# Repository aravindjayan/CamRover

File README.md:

# camRover

camRover is an ESP32-S3 rover platform with an OV7670 camera, two encoder-equipped DC motors, and addressable RGB LEDs. This repository contains the KiCad hardware design, release manufacturing files, and Arduino firmware used to bring up and test the board.

## Repository contents

- [`board_bringup/`](board_bringup/) — Arduino ESP32-S3 firmware for camera streaming over Wi-Fi and testing motors, quadrature encoders, and LEDs.
- [`camRover_pcb/camRover_pcb_v1_1/`](camRover_pcb/camRover_pcb_v1_1/) — KiCad v1.1 project, hierarchical schematics, PCB layout, assembly files, stencil outputs, and release Gerbers/drill files.
- [`camrover_img.jpg`](camrover_img.jpg) — photo of the built rover.

## Board bring-up firmware

The sketch captures OV7670 RGB565 frames at QVGA (320 × 240), converts them to JPEG, and serves a browser-based test page. The page shows the live video and provides motor pulses, encoder tests, and RGB LED controls. Motor commands have a 2-second firmware watchdog.

### Build with Arduino IDE

Build tested with **Arduino-ESP32 3.3.12**.

1. Open `board_bringup/board_bringup.ino` in Arduino IDE. Keep `sccb_ov7670_compat.cpp` in the same sketch folder.
2. Install/select the **Arduino-ESP32 3.3.12** board package.
3. Select **ESP32S3 Dev Module** and set:

   | Setting | Value |
   |---|---|
   | Flash Size | `16MB (128Mb)` |
   | PSRAM | `OPI PSRAM` |
   | USB CDC On Boot | `Enabled` |

4. Connect the ESP32-S3 board over USB, select its port, then compile and upload.
5. Open Serial Monitor at **115200 baud**. After Wi-Fi connects, open the printed IP address in a browser.

Before uploading, set `WIFI_SSID` and `WIFI_PASSWORD` near the top of `board_bringup.ino` to your 2.4 GHz Wi-Fi credentials. The defaults in the sketch are local development settings; replace them for your network. The rover and browser must be on the same network. If Wi-Fi does not connect, motor and LED serial commands remain available.

Camera orientation and left-edge crop can be adjusted with `CAMERA_ROTATION` (`0`, `90`, `180`, or `270`) and `CAMERA_CROP_LEFT` in the sketch.

### Bring-up controls

The web page provides:

- Live OV7670 video.
- Forward/reverse pulse tests for each motor and both motors together; each web pulse lasts 750 ms.
- Encoder count reset and forward/reverse tests. Lift wheels clear before running encoder tests.
- Red, green, blue, white, and off LED controls.

Serial commands at 115200 baud:

| Command | Action |
|---|---|
| `m <left> <right>` | Drive motors with values from `-255` to `255` (1-second timeout). |
| `s` | Stop motors. |
| `l <r> <g> <b>` | Set all five LEDs; each color value is `0`–`255`. |
| `e` | Print encoder counts. |

### Firmware pin map

| Function | ESP32-S3 GPIO |
|---|---|
| OV7670 D0–D7 | 4, 8, 5, 9, 6, 10, 7, 11 |
| OV7670 XCLK / PCLK / VSYNC / HREF | 13 / 12 / 21 / 14 |
| OV7670 SIOD / SIOC | 16 / 17 |
| Motor 1 DRV8871 IN1 / IN2 | 18 / 15 |
| Motor 2 DRV8871 IN1 / IN2 | 42 / 47 |
| Motor 1 encoder A / B | 41 / 40 |
| Motor 2 encoder A / B | 2 / 1 |
| WS2812B chain DIN (5 LEDs) | 48 |

## PCB files

Open `camRover_pcb/camRover_pcb_v1_1/camRover_pcb_v1_1.kicad_pro` in KiCad. The project includes the main schematic and hierarchical sheets for the ESP32, motor drive, and power circuitry, plus the PCB layout and assembly bill of materials.

The `CamRover_v1_1_Gerbers/` folder and `CamRover_v1_1_Gerbers.zip` contain the release copper, solder mask, paste, silkscreen, board outline, drill files, and drill maps for fabrication. Check the fabrication house’s layer and drill requirements before ordering.

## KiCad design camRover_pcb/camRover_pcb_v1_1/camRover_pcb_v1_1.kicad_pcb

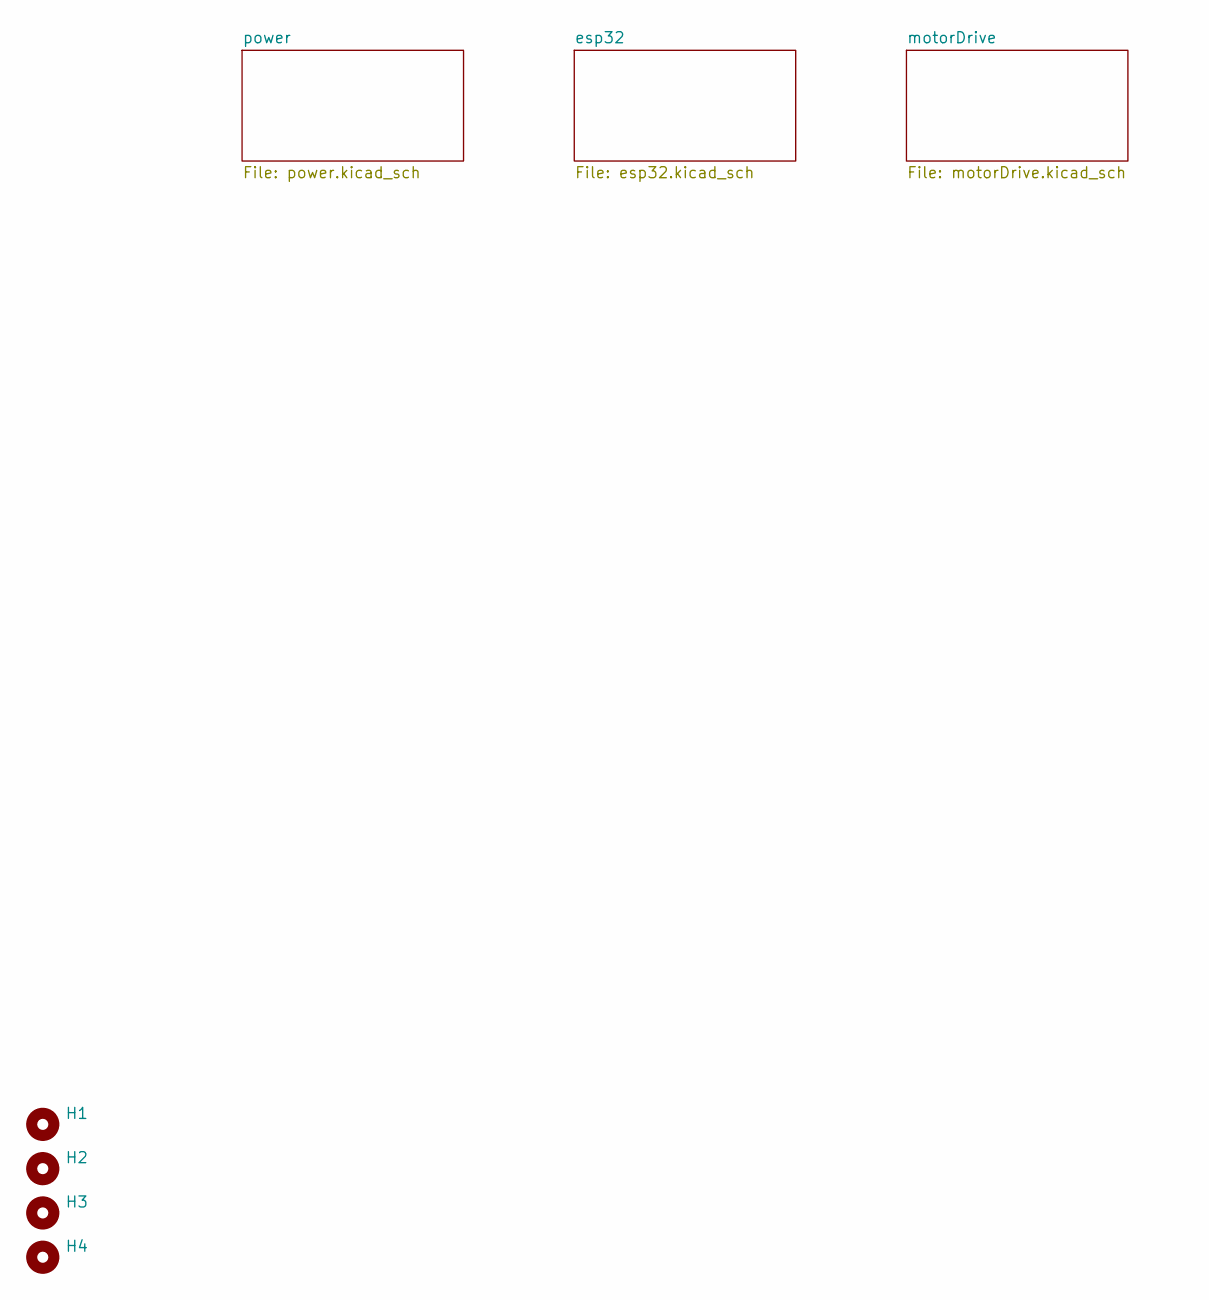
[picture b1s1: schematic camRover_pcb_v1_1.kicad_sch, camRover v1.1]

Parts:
H1, H2, H3, H4: MountingHole; MountingHole_3.2mm_M3

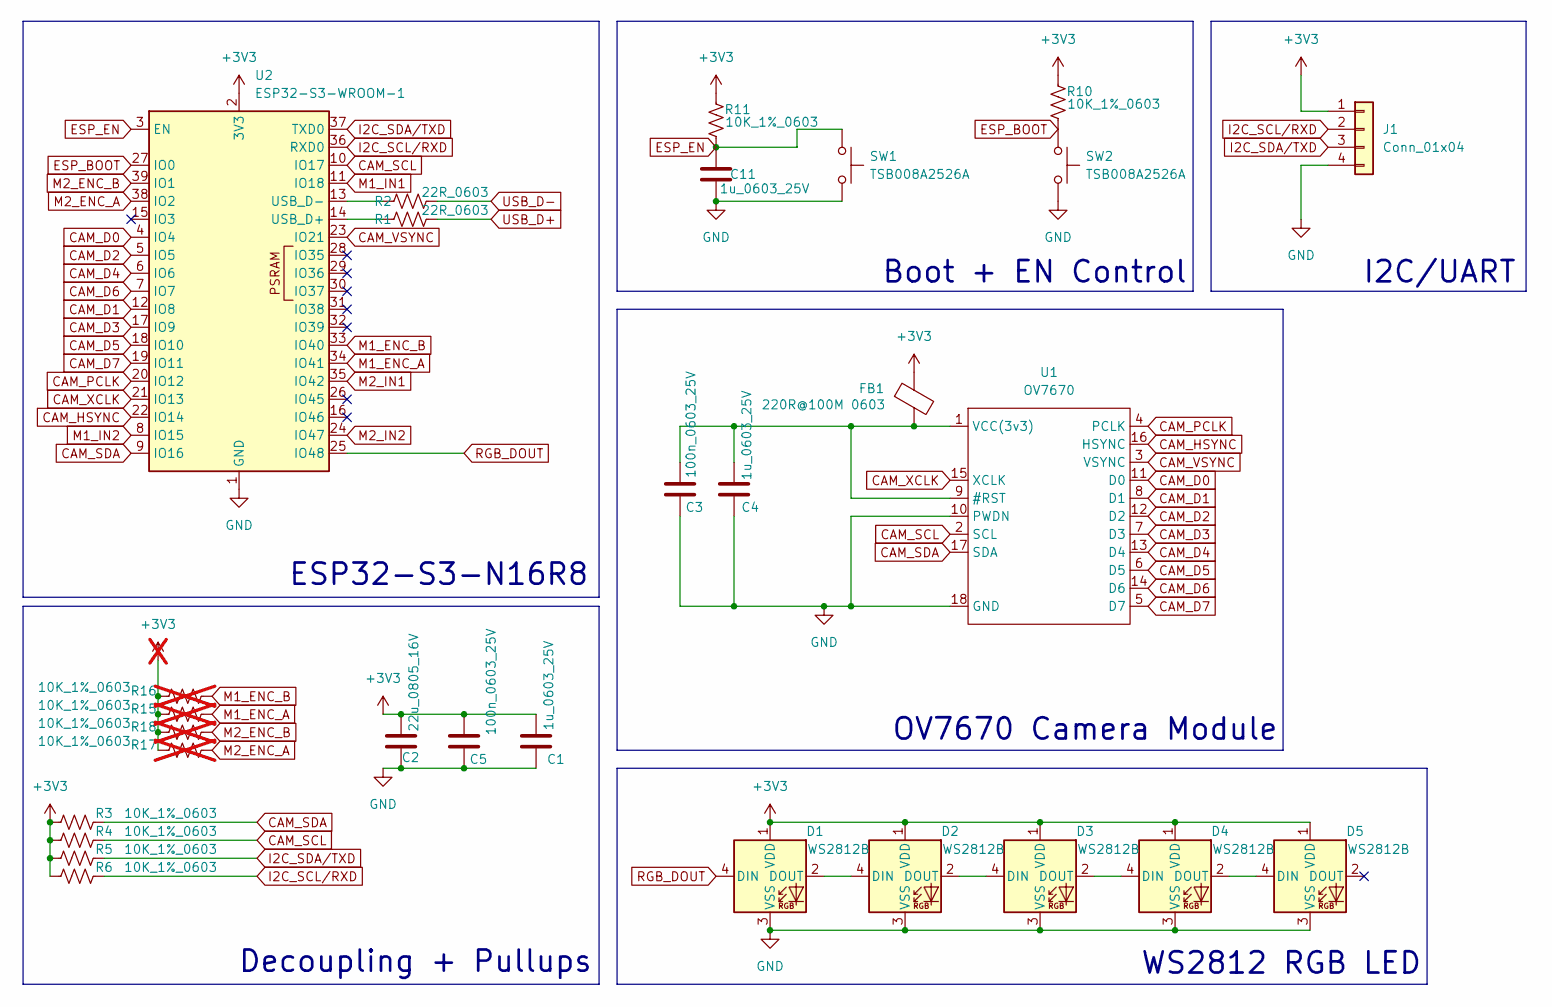
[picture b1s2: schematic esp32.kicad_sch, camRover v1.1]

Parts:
C1, C4, C11: 1u_0603_25V; C_0603_1608Metric
C2: 22u_0805_16V; C_0805_2012Metric
C3, C5: 100n_0603_25V; C_0603_1608Metric
D1, D2, D3, D4, D5: WS2812B; LED_WS2812B_PLCC4_5.0x5.0mm_P3.2mm
FB1: 220R@100M 0603; L_0603_1608Metric
J1: Conn_01x04; PinHeader_1x04_P2.54mm_Vertical
R1, R2: 22R_0603; R_0603_1608Metric
R3, R4, R5, R6, R10, R11: 10K_1%_0603; R_0603_1608Metric
R15, R16, R17, R18: 10K_1%_0603; R_0603_1608Metric; not fitted
SW1, SW2: TSB008A2526A; SW_SPST_CK_RS282G05A3
U1: OV7670; ov7670_dipModule
U2: ESP32-S3-WROOM-1

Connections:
+3V3: C1.1, C2.2, C5.1, D1.1 (VDD), D2.1 (VDD), D3.1 (VDD), D4.1 (VDD), D5.1 (VDD), FB1.1, J1.1, R3.2, R4.2, R5.2, R6.2, R10.1, R11.1, R15.2, R16.2, R17.2, R18.2, U2.2 (3V3); also elsewhere on the board
CAM_D0: U1.11 (D0), U2.4 (IO4)
CAM_D1: U1.8 (D1), U2.12 (IO8)
CAM_D2: U1.12 (D2), U2.5 (IO5)
CAM_D3: U1.7 (D3), U2.17 (IO9)
CAM_D4: U1.13 (D4), U2.6 (IO6)
CAM_D5: U1.6 (D5), U2.18 (IO10)
CAM_D6: U1.14 (D6), U2.7 (IO7)
CAM_D7: U1.5 (D7), U2.19 (IO11)
CAM_HSYNC: U1.16 (HSYNC), U2.22 (IO14)
CAM_PCLK: U1.4 (PCLK), U2.20 (IO12)
CAM_SCL: R4.1, U1.2 (SCL), U2.10 (IO17)
CAM_SDA: R3.1, U1.17 (SDA), U2.9 (IO16)
CAM_VSYNC: U1.3 (VSYNC), U2.23 (IO21)
CAM_XCLK: U1.15 (XCLK), U2.21 (IO13)
ESP_BOOT: R10.2, SW2.1, U2.27 (IO0)
ESP_EN: C11.1, R11.2, SW1.1, U2.3 (EN)
GND: C1.2, C2.1, C3.2, C4.2, C5.2, C11.2, D1.3 (VSS), D2.3 (VSS), D3.3 (VSS), D4.3 (VSS), D5.3 (VSS), J1.4, SW1.2, SW2.2, U1.10 (PWDN), U1.18 (GND), U2.1 (GND), U2.40 (GND), U2.41 (GND); also elsewhere on the board
I2C_SCL/RXD: J1.2, R6.1, U2.36 (RXD0)
I2C_SDA/TXD: J1.3, R5.1, U2.37 (TXD0)
M1_ENC_A: R15.1, U2.34 (IO41); also elsewhere on the board
M1_ENC_B: R16.1, U2.33 (IO40); also elsewhere on the board
M1_IN1: U2.11 (IO18); also elsewhere on the board
M1_IN2: U2.8 (IO15); also elsewhere on the board
M2_ENC_A: R17.1, U2.38 (IO2); also elsewhere on the board
M2_ENC_B: R18.1, U2.39 (IO1); also elsewhere on the board
M2_IN1: U2.35 (IO42); also elsewhere on the board
M2_IN2: U2.24 (IO47); also elsewhere on the board
unnamed: D1.2 (DOUT), D2.4 (DIN)
unnamed: D2.2 (DOUT), D3.4 (DIN)
unnamed: D3.2 (DOUT), D4.4 (DIN)
unnamed: D4.2 (DOUT), D5.4 (DIN)
unnamed: C3.1, C4.1, FB1.2, U1.1 (VCC(3v3)), U1.9 (#RST)
unnamed: R1.1, U2.14 (USB_D+)
unnamed: R2.1, U2.13 (USB_D-)
RGB_DOUT: D1.4 (DIN), U2.25 (IO48)
USB_D+: R1.2; also elsewhere on the board
USB_D-: R2.2; also elsewhere on the board

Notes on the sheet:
I2C/UART
OV7670 Camera Module
Decoupling + Pullups
ESP32-S3-N16R8
WS2812 RGB LED
Boot + EN Control

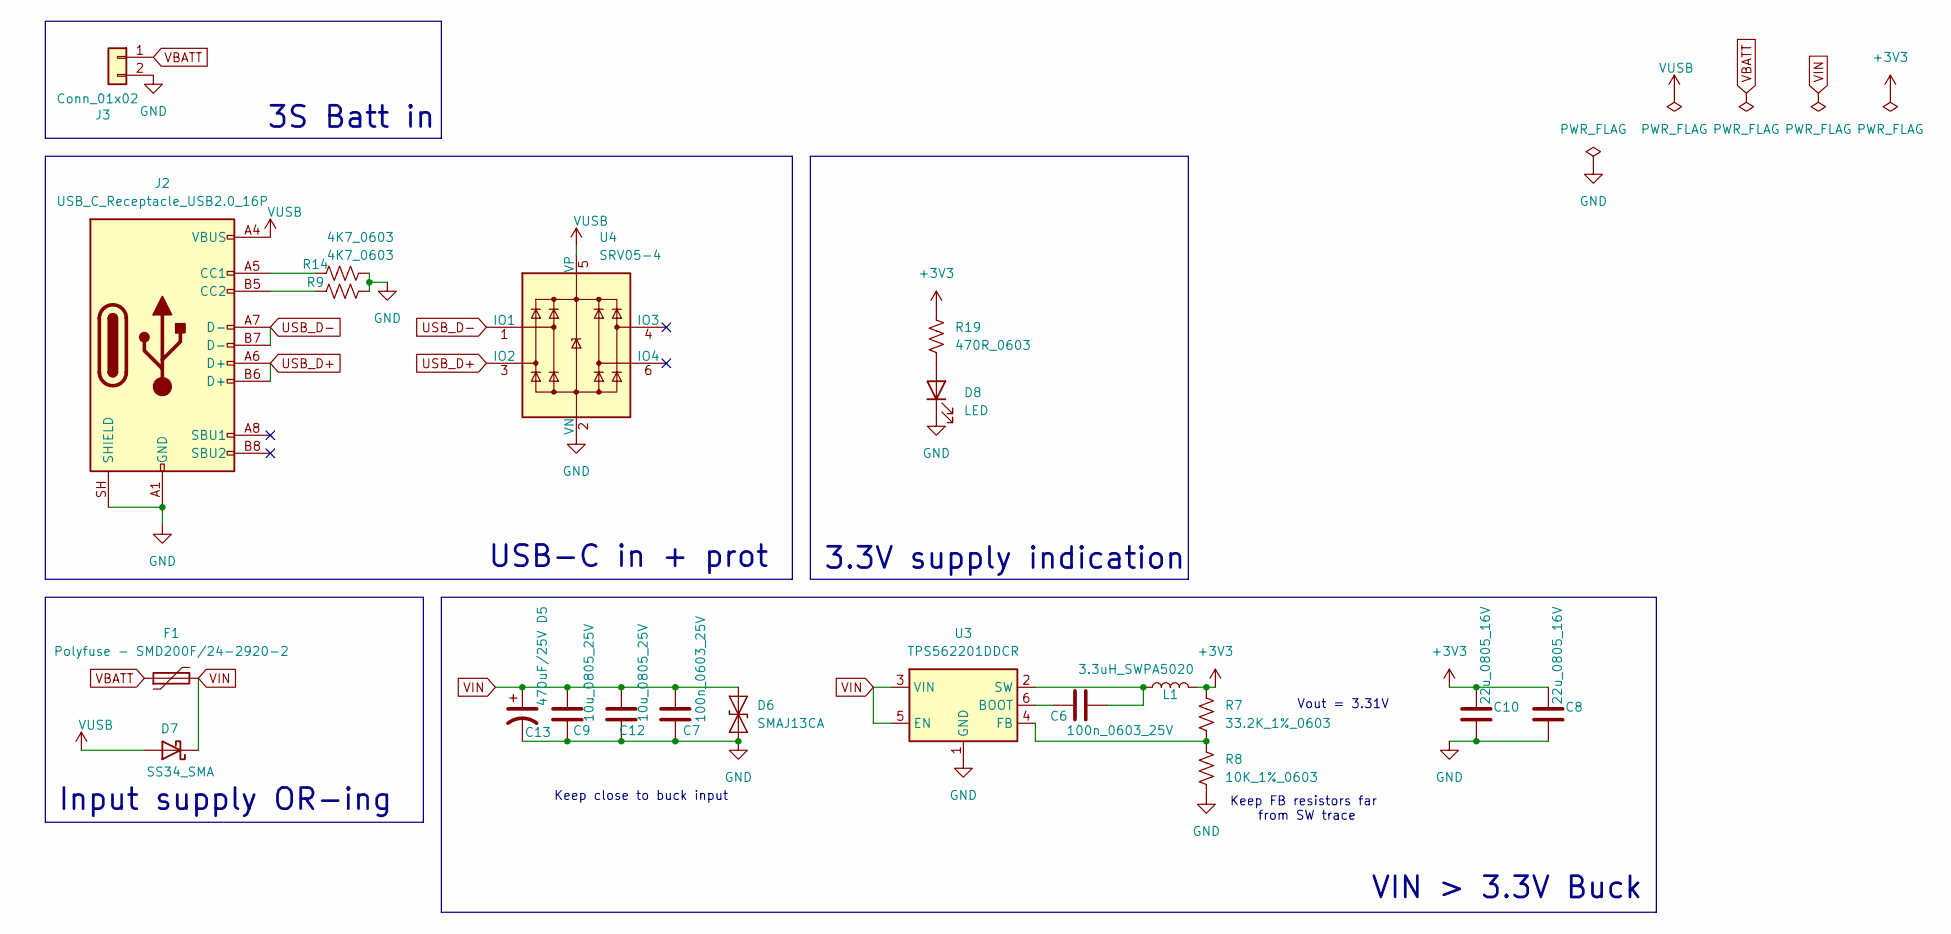
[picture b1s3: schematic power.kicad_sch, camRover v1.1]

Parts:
C6, C7: 100n_0603_25V; C_0603_1608Metric
C8, C10: 22u_0805_16V; C_0805_2012Metric
C9, C12: 10u_0805_25V; C_0805_2012Metric
C13: 470uF/25V D5; CP_Radial_D6.3mm_P2.50mm
D6: SMAJ13CA; D_SMA
D7: SS34_SMA; D_SMA
D8: LED; LED_0805_2012Metric
F1: Polyfuse - SMD200F/24-2920-2; Fuse_2920_7451Metric
J2: USB_C_Receptacle_USB2.0_16P; USB_C_Receptacle_U263-163N-4WS1735-XKB
J3: Conn_01x02; SolderWire-1.5sqmm_1x02_P7.8mm_D1.7mm_OD3.9mm
L1: 3.3uH_SWPA5020; L_Sunlord_SWPA5020S
R7: 33.2K_1%_0603; R_0603_1608Metric
R8: 10K_1%_0603; R_0603_1608Metric
R9, R14: 4K7_0603; R_0603_1608Metric
R19: 470R_0603; R_0603_1608Metric
U3: TPS562201DDCR; SOT-23-6
U4: SRV05-4; SOT-23-6

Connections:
+3V3: C8.2, C10.2, L1.2, R7.2, R19.2; also elsewhere on the board
GND: C7.2, C8.1, C9.2, C10.1, C12.2, C13.2, D6.1 (A1), D8.1 (K), J2.A1 (GND), J2.A12 (GND), J2.B1 (GND), J2.B12 (GND), J2.SH (SHIELD), J3.2, R8.1, R9.2, R14.2, U3.1 (GND), U4.2 (VN); also elsewhere on the board
unnamed: D8.2 (A), R19.1
unnamed: J2.A5 (CC1), R14.1
unnamed: J2.B5 (CC2), R9.1
unnamed: C6.1, U3.6 (BOOT)
unnamed: R7.1, R8.2, U3.4 (FB)
unnamed: C6.2, L1.1, U3.2 (SW)
USB_D+: J2.A6 (D+), J2.B6 (D+), U4.3 (IO2); also elsewhere on the board
USB_D-: J2.A7 (D-), J2.B7 (D-), U4.1 (IO1); also elsewhere on the board
VBATT: F1.1, J3.1
VIN: C7.1, C9.1, C12.1, C13.1, D6.2 (A2), D7.1 (K), F1.2, U3.3 (VIN), U3.5 (EN); also elsewhere on the board
VUSB: D7.2 (A), J2.A4 (VBUS), J2.A9 (VBUS), J2.B4 (VBUS), J2.B9 (VBUS), U4.5 (VP)

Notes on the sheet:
3S Batt in
Keep close to buck input
VIN > 3.3V Buck
Vout = 3.31V
USB-C in + prot
Keep FB resistors far from SW trace
Input supply OR-ing
3.3V supply indication

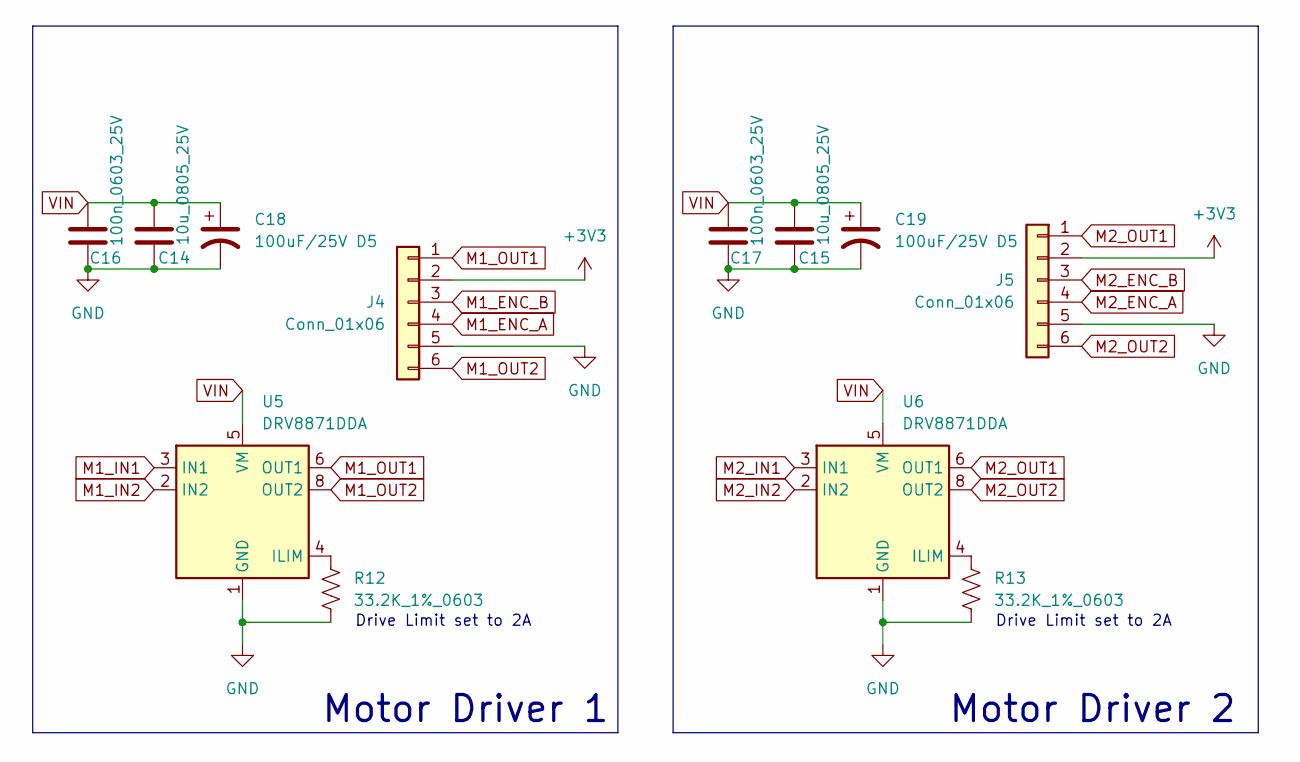
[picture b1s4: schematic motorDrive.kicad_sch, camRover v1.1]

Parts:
C14, C15: 10u_0805_25V; C_0805_2012Metric
C16, C17: 100n_0603_25V; C_0603_1608Metric
C18, C19: 100uF/25V D5; CP_Radial_D5.0mm_P2.00mm
J4, J5: Conn_01x06; 6pin_wireConn_2.54p
R12, R13: 33.2K_1%_0603; R_0603_1608Metric
U5, U6: DRV8871DDA; Texas_HTSOP-8-1EP_3.9x4.9mm_P1.27mm_EP2.95x4.9mm_Mask2.4x3.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

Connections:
+3V3: J4.2, J5.2; also elsewhere on the board
GND: C14.2, C15.2, C16.2, C17.2, C18.2, C19.2, J4.5, J5.5, R12.1, R13.1, U5.1 (GND), U5.7 (GND), U5.9 (GND), U6.1 (GND), U6.7 (GND), U6.9 (GND); also elsewhere on the board
M1_ENC_A: J4.4; also elsewhere on the board
M1_ENC_B: J4.3; also elsewhere on the board
M1_IN1: U5.3 (IN1); also elsewhere on the board
M1_IN2: U5.2 (IN2); also elsewhere on the board
M1_OUT1: J4.1, U5.6 (OUT1)
M1_OUT2: J4.6, U5.8 (OUT2)
M2_ENC_A: J5.4; also elsewhere on the board
M2_ENC_B: J5.3; also elsewhere on the board
M2_IN1: U6.3 (IN1); also elsewhere on the board
M2_IN2: U6.2 (IN2); also elsewhere on the board
M2_OUT1: J5.1, U6.6 (OUT1)
M2_OUT2: J5.6, U6.8 (OUT2)
unnamed: R12.2, U5.4 (ILIM)
unnamed: R13.2, U6.4 (ILIM)
VIN: C14.1, C15.1, C16.1, C17.1, C18.1, C19.1, U5.5 (VM), U6.5 (VM); also elsewhere on the board

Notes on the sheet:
Drive Limit set to 2A
Motor Driver 2
Motor Driver 1

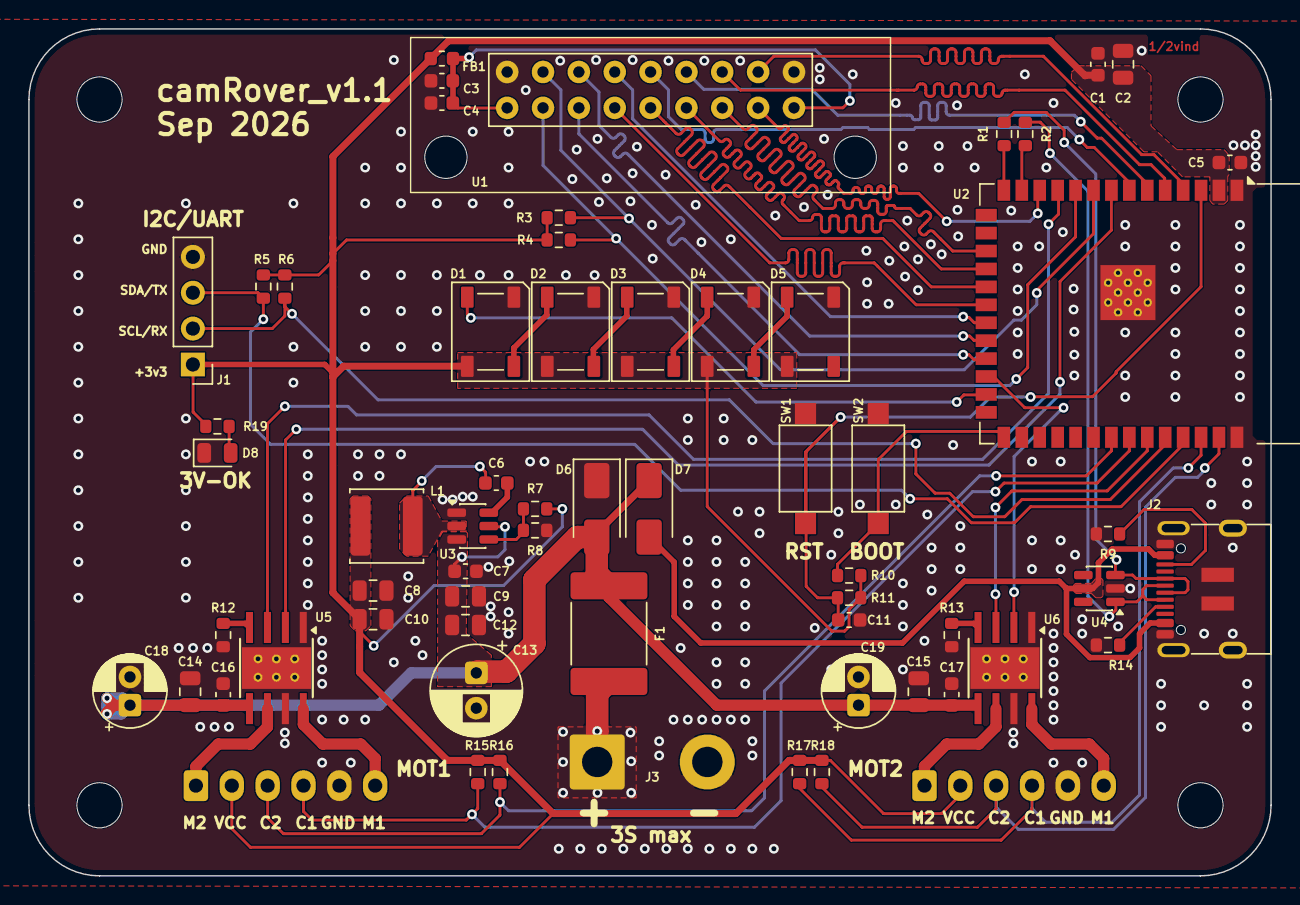
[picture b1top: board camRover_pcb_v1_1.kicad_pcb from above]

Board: 2 copper layers, 88.0 x 60.0 mm, 66 parts (0 on the bottom side), 53 nets.

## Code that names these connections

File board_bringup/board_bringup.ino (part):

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const char *WIFI_PASSWORD = "";

// OV7670 wiring from camRover PCB.
static constexpr int CAM_D0 = 4;
static constexpr int CAM_D1 = 8;
static constexpr int CAM_D2 = 5;
static constexpr int CAM_D3 = 9;
static constexpr int CAM_D4 = 6;
static constexpr int CAM_D5 = 10;
static constexpr int CAM_D6 = 7;
static constexpr int CAM_D7 = 11;
static constexpr int CAM_XCLK = 13;
static constexpr int CAM_PCLK = 12;
static constexpr int CAM_VSYNC = 21;
static constexpr int CAM_HREF = 14;
static constexpr int CAM_SIOD = 16;
static constexpr int CAM_SIOC = 17;
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static constexpr int CAM_PWDN = -1;

// Motor, encoder, and RGB nets from camRover_pcb_v1.
static constexpr int M1_IN1 = 18;
static constexpr int M1_IN2 = 15;
static constexpr int M2_IN1 = 42;
static constexpr int M2_IN2 = 47;
static constexpr int M1_ENC_A = 41;
static constexpr int M1_ENC_B = 40;
static constexpr int M2_ENC_A = 2;
static constexpr int M2_ENC_B = 1;
static constexpr int RGB_DOUT = 48;
static constexpr int RGB_LED_COUNT = 5;

// Camera mounting options. Allowed rotations: 0, 90, 180, 270 degrees clockwise.
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    digitalWrite(M1_IN2, LOW);
    digitalWrite(M2_IN1, LOW);
    digitalWrite(M2_IN2, LOW);
    pinMode(M1_IN1, OUTPUT);
    pinMode(M1_IN2, OUTPUT);
    pinMode(M2_IN1, OUTPUT);
    pinMode(M2_IN2, OUTPUT);
}

static void setLed(uint8_t red, uint8_t green, uint8_t blue) {
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    camera_config_t config = {};
    config.ledc_channel = LEDC_CHANNEL_0;
    config.ledc_timer = LEDC_TIMER_0;
    config.pin_d0 = CAM_D0;
    config.pin_d1 = CAM_D1;
    config.pin_d2 = CAM_D2;
    config.pin_d3 = CAM_D3;
    config.pin_d4 = CAM_D4;
    config.pin_d5 = CAM_D5;
    config.pin_d6 = CAM_D6;
    config.pin_d7 = CAM_D7;
    config.pin_xclk = CAM_XCLK;
    config.pin_pclk = CAM_PCLK;
    config.pin_vsync = CAM_VSYNC;
    config.pin_href = CAM_HREF;
    config.pin_sccb_sda = CAM_SIOD;
    config.pin_sccb_scl = CAM_SIOC;
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    ledcAttachChannel(M2_IN2, MOTOR_PWM_HZ, MOTOR_PWM_BITS, 5);
    stopMotors();

    pinMode(M1_ENC_A, INPUT_PULLUP);
    pinMode(M1_ENC_B, INPUT_PULLUP);
    pinMode(M2_ENC_A, INPUT_PULLUP);
    pinMode(M2_ENC_B, INPUT_PULLUP);
    resetEncoders();
    attachInterrupt(digitalPinToInterrupt(M1_ENC_A), encoder1ISR, CHANGE);
    attachInterrupt(digitalPinToInterrupt(M1_ENC_B), encoder1ISR, CHANGE);
    attachInterrupt(digitalPinToInterrupt(M2_ENC_A), encoder2ISR, CHANGE);
    attachInterrupt(digitalPinToInterrupt(M2_ENC_B), encoder2ISR, CHANGE);
    rgbReady = rmtInit(RGB_DOUT, RMT_TX_MODE, RMT_MEM_NUM_BLOCKS_3, 10000000);
    setLed(0, 0, 12);
}
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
